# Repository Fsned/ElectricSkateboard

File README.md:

# ElectricSkateboard

This is my repo to contain all my files while making my own electric skateboard.

## BatteryIndicator
This is the part to indicate the current battery charge remaining on each battery, without the battery is connected to the skateboard.
This is done by reading the battery information from the BMS via UART, to a Xiao RP2040 MCU, and displaying it on a 10-LED RGB strip.
The LED-strip should be visible from the outside.
Stuff i make myself:
- PCB to connect everything
- Software to read UART and control the LED's accordingly

## Batterycase
This is the case, containing the batterypack, the BMS and the battery-indicator. This should eventually have some fancy
slide-in male connector, to latch on and connect to the motor controller.

## MC case
This is the case containing the motor controller and remote receiver, communicating with the remote.
This should have a slide-in female part, to easily connect to the batterycase.

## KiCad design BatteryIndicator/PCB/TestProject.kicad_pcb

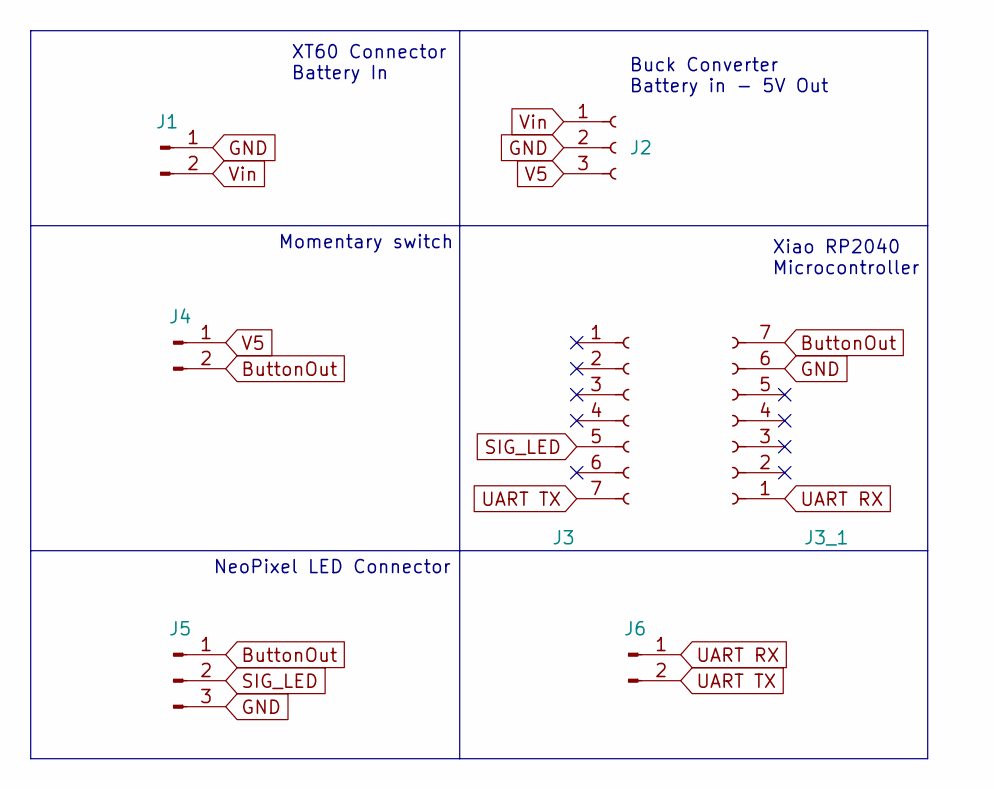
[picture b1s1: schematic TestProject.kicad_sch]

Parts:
J1: Conn_01x02_Male; AMASS_XT60-M_1x02_P7.20mm_Vertical
J2: Conn_01x03_Female; PinSocket_1x03_P2.54mm_Vertical
J3, J3_1: Conn_01x07_Female; PinSocket_1x07_P2.54mm_Vertical
J4, J6: Conn_01x02_Male; PinHeader_1x02_P2.54mm_Vertical
J5: Conn_01x03_Male; PinHeader_1x03_P2.54mm_Vertical

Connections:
ButtonOut: J3_1.7, J4.2, J5.1
GND: J1.1, J2.2, J3_1.6, J5.3
SIG_LED: J3.5, J5.2
UART RX: J3_1.1, J6.1
UART TX: J3.7, J6.2
V5: J2.3, J4.1
Vin: J1.2, J2.1

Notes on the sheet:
Momentary switch
NeoPixel LED Connector
XT60 Connector Battery In
Xiao RP2040 Microcontroller
Buck Converter Battery in - 5V Out

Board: 2 copper layers, 7 parts (1 on the bottom side), 7 nets, no tracks yet.

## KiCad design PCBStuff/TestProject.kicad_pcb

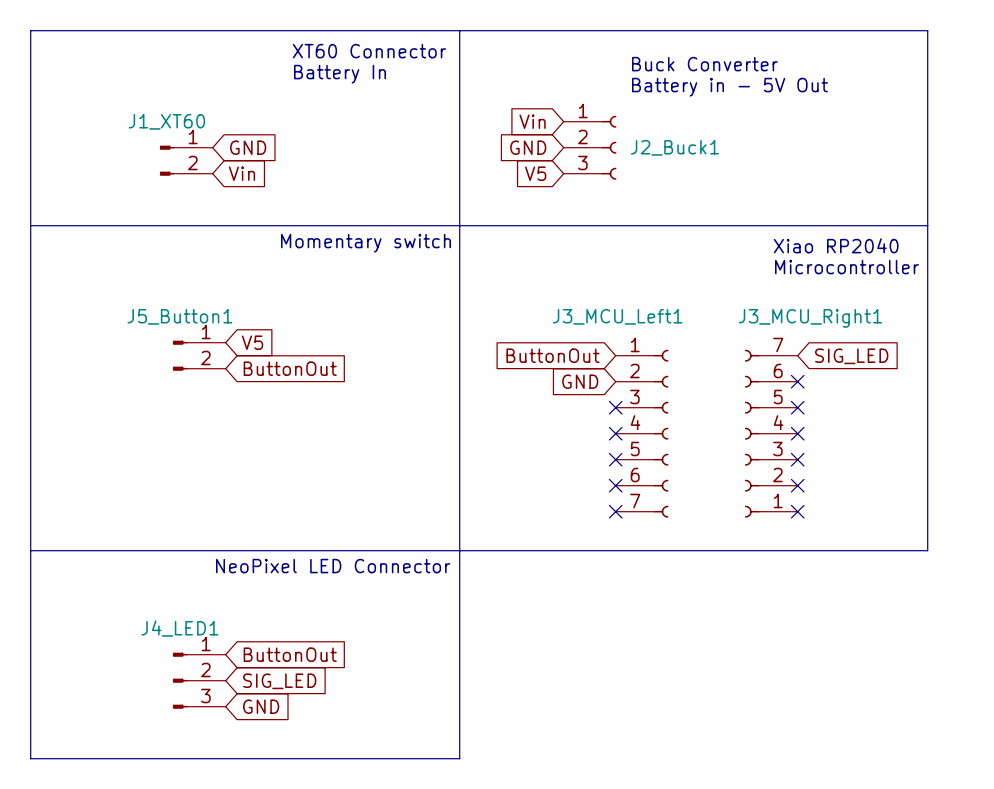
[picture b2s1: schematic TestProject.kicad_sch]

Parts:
J1_XT60: Conn_01x02_Male; AMASS_XT60-M_1x02_P7.20mm_Vertical
J2_Buck1: Conn_01x03_Female; PinSocket_1x03_P2.54mm_Vertical
J3_MCU_Left1, J3_MCU_Right1: Conn_01x07_Female; PinSocket_1x07_P2.54mm_Vertical
J4_LED1: Conn_01x03_Male; PinSocket_1x03_P2.54mm_Vertical
J5_Button1: Conn_01x02_Male; PinHeader_1x02_P2.54mm_Vertical

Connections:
ButtonOut: J3_MCU_Left1.1, J4_LED1.1, J5_Button1.2
GND: J1_XT60.1, J2_Buck1.2, J3_MCU_Left1.2, J4_LED1.3
SIG_LED: J3_MCU_Right1.7, J4_LED1.2
V5: J2_Buck1.3, J5_Button1.1
Vin: J1_XT60.2, J2_Buck1.1

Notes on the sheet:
Momentary switch
NeoPixel LED Connector
XT60 Connector Battery In
Xiao RP2040 Microcontroller
Buck Converter Battery in - 5V Out

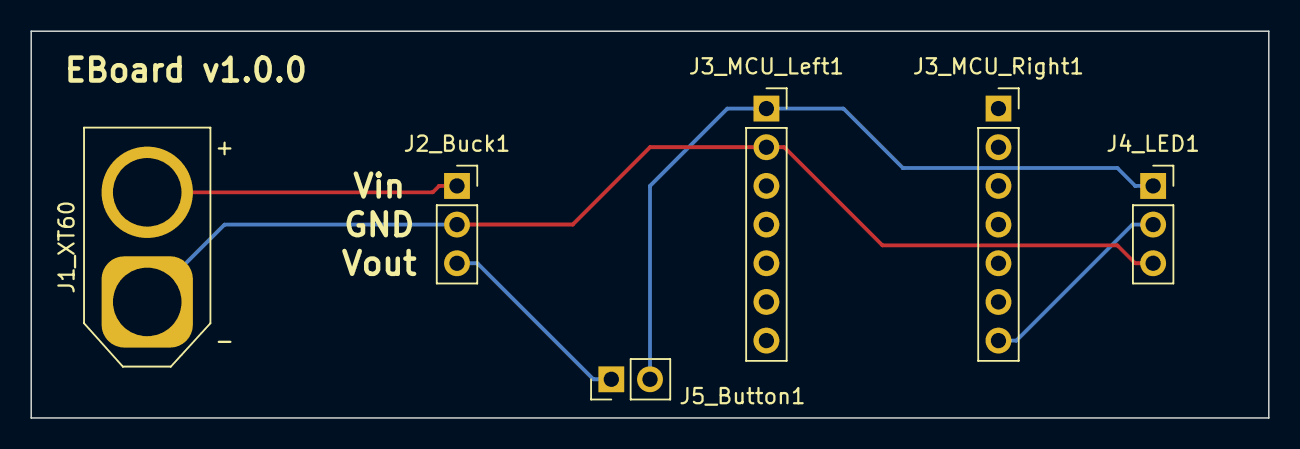
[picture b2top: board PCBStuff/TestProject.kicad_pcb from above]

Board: 2 copper layers, 81.3 x 25.4 mm, 6 parts (0 on the bottom side), 5 nets.

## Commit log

2022-04-05 First commit!
2022-04-05 Made a first draft for EBoard
2022-04-05 Made new gerbers including drillfile to make holes in jlcpcb
2022-04-06 Fixed footprint of MCU, re-organized header layout to shrink overall boardsize
2022-04-06 Re-did file structure to better scale to multiple topics
2022-04-07 Added sourcefiles from PlatformIO on desktop
2022-04-11 Added UART pins to PCB
2022-04-11 Re-added mounting holes
2022-04-11 Don't know what i did :P
2022-04-21 Tried to redo some layout on the PCB
2022-04-21 edited pcb
2022-04-26 Fixed some markings, changed version to mk1.1
